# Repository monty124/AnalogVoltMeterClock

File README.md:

# AnalogVoltMeterClock
An AnalogVoltMeterClock 🤷‍♂️

# What is this?
Just a fun project to show the time in another way

Inspiration from:

- https://hackaday.io/project/163977-esp8266-wifi-ntp-voltmeter-clock
- https://michaelteeuw.nl/post/what-time-is-it-fathers-day
- https://github.com/MichMich/AnalogVoltMeterClock

# I want one

Sure, youll need:

### BOM

- An Enclosure, it needs to be big enough to fit the analog dials as well as the PCB (100x60) <br>
  There is a printable one that MAY work here https://www.thingiverse.com/thing:3437800 BUT i am unsure if my PCB will fit this enclosure. Zip Files are committed in this git repo if you want to try it; OR build without the PCB and hard wire to the ESP module and use this one.
- Optional 3D printed back or solid back, (make room for your power connection!)
- 3x Analog Voltmeter SO-45 style gauges (voltage unimportant) <br>
  https://www.aliexpress.com/item/1005003489268646.html <br>
  
- 3x 3.9K Resistors OR any value between 2 - 5 K however you will need to work out your own calibration matrix
- PCB (gerber files are included [here](/AnalogVoltMeterClock/Gerber))

- "SW-420" Vibration Sensor <br>
  https://www.aliexpress.com/item/1005006205428052.html <br>
  
- "6 Pin" USB C Power socket OR panel mount DC socket and 5V power supply (use PWR header and omit USB) <br>
   <br>
  https://www.aliexpress.com/item/32976798070.html
- 3.5mm Pitch 2P and 3P Screw Terminals <br>
   https://www.aliexpress.com/item/4000874208361.html <br>
    
- 1x FreeNove ESP32 WROOM 32E (not S3 variants) <br>
  https://store.freenove.com/products/fnk0090 or on Aliexpress<br>
  Note, Pinout of PCB is not compatible with other ESP modules like DevKit, etc <br>
 
- SN74AHCT125N IC <br>
 https://www.digikey.com.au/en/products/detail/texas-instruments/SN74AHCT125N/375798
- suitable 14Pin DIP Socket (optional) e.g. <br>
 https://www.digikey.com.au/en/products/detail/cnc-tech/245-14-1-03/3441580 <br>
- 2.54 Headers and Sockets (optional) <br>
  Socket 2x 20 pin for ESP module <br>
  Header for Power (if desired) <br>
- SK6812 LED's (ON PCB!) (if other variants are used like WS2812B you will need to debug the light: code block slightly) <br>
  https://esphome.io/components/light/index.html <br>
  n.b the White Channel is not important, can be WW, CW or NW <br>
  https://www.aliexpress.com/item/32961777888.html <br>
  https://www.aliexpress.com/item/1005002509850925.html <br>
   <br>
  <br>
- Silicone Hookup Wire and Crimps
- ESPHome Dev environment to build and deploy the Image <br>
  https://esphome.io/guides/getting_started_command_line <br>
  https://esphome.io/guides/getting_started_hassio <br>
- Cut and Printed [stickers](/Gauges)) to replace voltmeter gauge; use the PDF or the svg can be edited and printed with Inkscape https://inkscape.org/ <br>

# How To!

- Obtain your BOM items
- Build your enclosure!
- Dissasemble your gauges, replace the existing resistors with the 3.9K resistors, wire and mount your LED's <br>
   <br>
- Stick your gauge sticker over the original faceplace
- REASSEMBLE! <br>
   <br>
- Assemble your PCB
- Write the Base esphome image to your module https://web.esphome.io/ and connect to WIFI remember to also to include the `.h` files
- Edit the ESPHome Yaml file where required 
  - set MIN and MAX PWM
  - (optional) RGBW and Bright values
  - TimeZone (if not AEST) and or change to sntp see below
  - Disable Home Assistant api (remove encryption and key) if you dont use HA (also change time to sntp) <br>
    i.e:
    ```
    - platform: sntp
    #- platform: homeassistant
    timezone: Australia/Brisbane
    ```

- Build and Write the config to the module
- All should be working! 
- Connect to the Module Web Page and set LED colour
- Import into Home Assistant (optional)

# Calibration

[Excel sheets](/SpreadSheets) added to help calibrate! 

## PWM

- Use the Module web page to test values:
- Set Calibrate to ON <br>
  <br>
- Find your MIN and MAX needle values for Hour, Minute and Second using the HOUR CALIBRATE, MIN CALIBRATE and SEC CALIBRATE Sliders, take note of the blue number <br>
 <br>
- Min the needle should be set to the desired minimum value (for example minimum values): <br>
 <br>
- Max is the same but the Maximum value (12 for Hour, and 60 for Min and Sec) <br>
- These numbers are recorded in the yaml file: <br>
   <br>
- This is the minimum amount of calibration required however you MUST set the "Average Gauge Needle" option to ON!

## Fine Tuned Calibration

- Continue to find each value and create a value MAP. <br>
- For example for Hour:
- find each PWM value for each number from 1 to 12
- Record the PWM values in `writeHandler.h` under `const int HOUR_NEEDLE[]` where each value represents the hour, the MAP works as such: <br>
  
  ```
  Midnight (12), 1 AM, 2, 3, 4, 5, 6, 7, 8, 9, 10, 11, 12, 1 PM, 2, 3, 4, 5, 6, 7, 8, 9, 10, 11
  ```

  DO NOT ALTER `const int HOUR_LOOKUP[]`

For Minute and Second there is a map for each second/minute, this can be performed by finding each PWM value per 5 interval (5 Seconds or 5 Minutes) THEN averaging the seconds and minutes in between. You are looking for as even as a spread between each minute/second represented as a whole integer 

  For example:

| Hour | PWM | Comment |
| :--: | :--: | :--: | 
| 0 | 14 | measured |
| 5 | 30 | measured |
| 10 | 48 | measured |

| Hour | PWM | Comment |
| :--: | :--: | :--: | 
| 0 | 14 | measured |
| 1 | 17 | averaged |
| 2 | 20 | averaged |
| 3 | 23 | averaged |
| 4 | 26 | averaged |
| 5 | 30 | measured |

Create a Map of all values and replace `const int SECOND_NEEDLE[]` and `const int MINUTE_NEEDLE[]`

You are able to fine tune the needle using the screw on the front of the dial

## LED

- enable LED: Calibrate
- To find your desired colour use 
  - LED: Blue Level
  - LED: Colour Brightness
  - LED: Green Level
  - LED: Red Level
  - LED: White Level

This value will save into eeprom but will not be retained if the module is reflashed, you can code these into the globals but!

## U2 Jumpers

The SN74AHCT125N can be a little .... sensitive and as we are only using one input and output a circuit has been built in where by if you accidently blow input/output 1A/1Y you can reconfgure the jumpers to use the other inputs and outputs! This avoids you throwing away an IC because one IO has failed. Hopefully.

 <br>

This table should help explain what jumpers you need to bridge. Note you will need to CUT the DEFAULT jumpers on JP3 and JP4 if you wish to use IO's 3 or 4, and cut the DEFAULT jumper on JP1 and JP5 to use IO 2

 <br>

More info can be found in the datasheet in the [repo](/sn74ahct125.pdf)

## To Do!

- Integrate a PCF8563 RTC module option for time keeping offline https://www.aliexpress.com/item/1005006438572175.html
- Code Improvements and tidy up
- ~~Excel sheet for calibration~~
- ~~Document matrix for IC~~
- 3D rear cover (STARTED!)
- Actual Assembly (still waiting on parts!)
- gif of movement

## I Wanna Contribute!

Sure, fork the repo and do ya thing then request a PR to merge!

## I found a bug or an Improvement!

As above OR open an Issue and lets see if we can fix

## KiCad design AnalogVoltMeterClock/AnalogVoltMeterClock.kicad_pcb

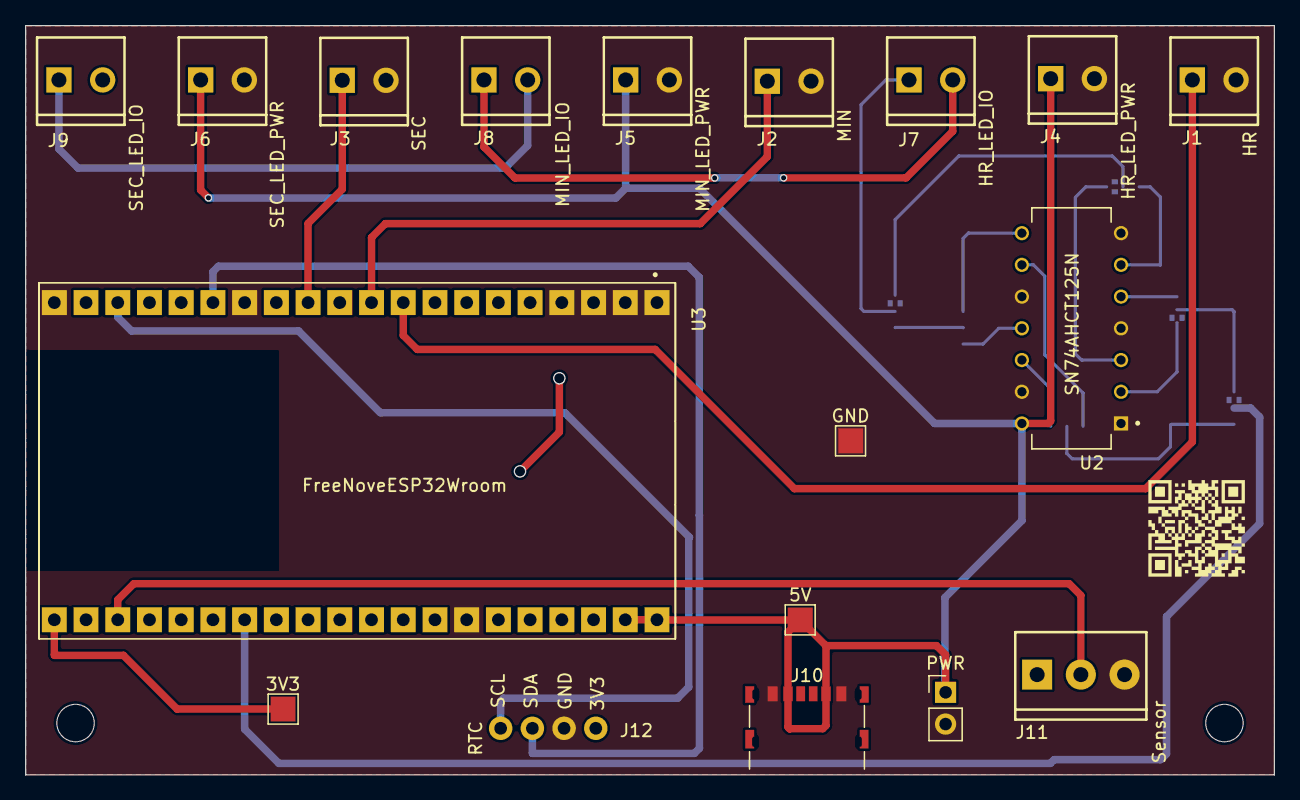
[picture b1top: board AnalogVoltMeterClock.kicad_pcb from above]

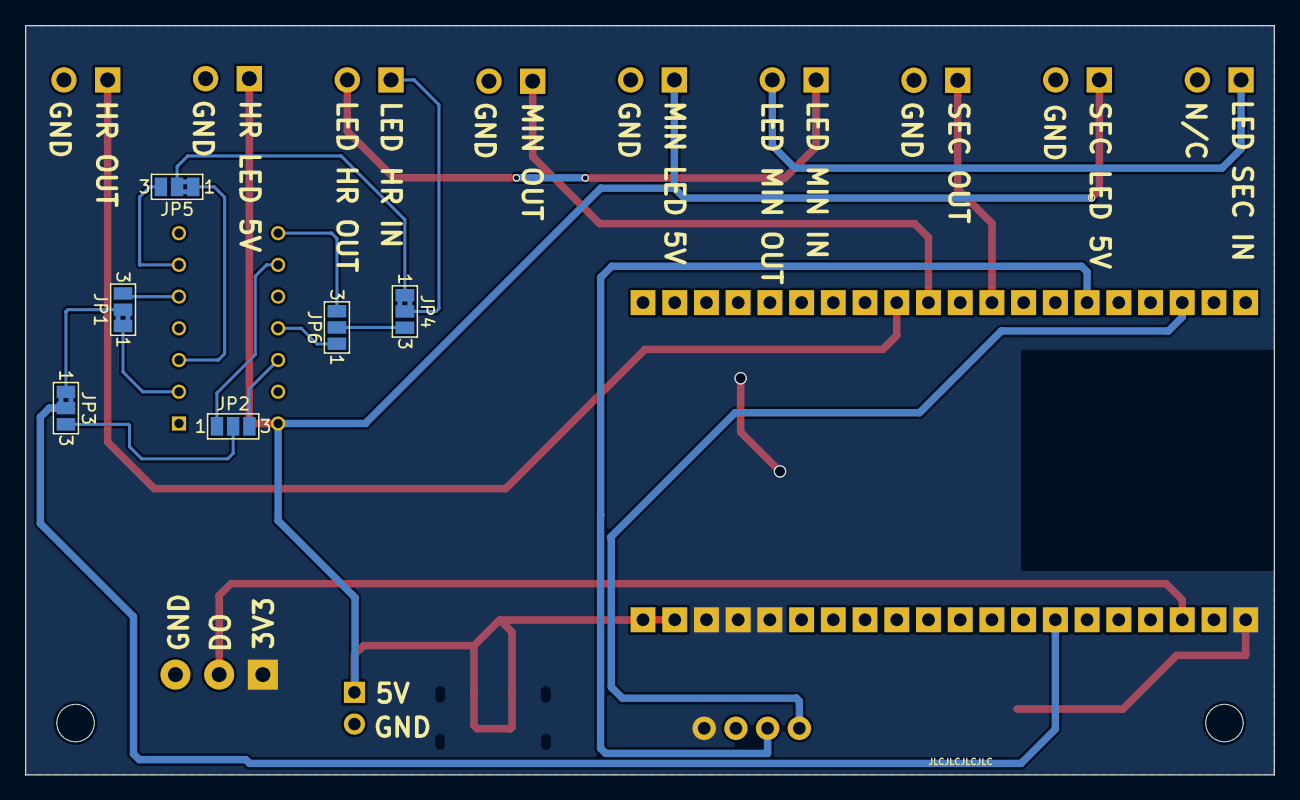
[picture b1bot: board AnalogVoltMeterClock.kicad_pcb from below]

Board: 2 copper layers, 100.0 x 60.0 mm, 26 parts (6 on the bottom side), 25 nets.

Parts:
3V3, 5V: TestPoint_Pad_2.0x2.0mm
GND: TestPoint_Pad_2.0x2.0mm
H1, H2: MountingHole; MountingHole_3mm
J1: HR; SCREWTERMINAL-3.5MM-2
J2: MIN; SCREWTERMINAL-3.5MM-2
J3: SEC; SCREWTERMINAL-3.5MM-2
J4: HR_LED_PWR; SCREWTERMINAL-3.5MM-2
J5: MIN_LED_PWR; SCREWTERMINAL-3.5MM-2
J6: SEC_LED_PWR; SCREWTERMINAL-3.5MM-2
J7: HR_LED_IO; SCREWTERMINAL-3.5MM-2
J8: MIN_LED_IO; SCREWTERMINAL-3.5MM-2
J9: SEC_LED_IO; SCREWTERMINAL-3.5MM-2
J10: PowerIn; USB_C_Receptacle_GCT_USB4135-GF-A_6P_TopMnt_Thru
J11: Sensor; SCREWTERMINAL-3.5MM-3
J12: RTC; 1X04
JP1: IO1_2-In; SolderJumper-3_P1.3mm_Bridged2Bar12_Pad1.0x1.5mm_NumberLabe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
JP2: IO3_4-In; SolderJumper-3_P1.3mm_Open_Pad1.0x1.5mm_NumberLabels
JP3, JP4: IO_12_34; SolderJumper-3_P1.3mm_Bridged2Bar12_Pad1.0x1.5mm_NumberLabe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
JP5: IO1_2-Out; SolderJumper-3_P1.3mm_Bridged2Bar12_Pad1.0x1.5mm_NumberLabe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
JP6: IO3_4-Out; SolderJumper-3_P1.3mm_Open_Pad1.0x1.5mm_NumberLabels
PWR: PinHeader_1x02_P2.54mm_Vertical
U2: SN74AHCT125N; DIP794W45P254L1930H508Q14
U3: FreeNoveESP32Wroom

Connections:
1A: JP1.1 (A), U2.2 (1A)
1Y: JP5.1 (A), U2.3 (1Y)
2A: JP1.3 (B), U2.5 (2A)
2Y: JP5.3 (B), U2.6 (2Y)
3A: JP2.1 (A), U2.9 (3A)
3V3: 3V3.1, J11.1, J12.1, U3.21 (3V3), U3.36 (3V3), U3.37 (3V3), U3.38 (3V3)
3Y: JP6.3 (B), U2.8 (3Y)
4A: JP2.3 (B), U2.12 (4A)
4Y: JP6.1 (A), U2.11 (4Y)
+5V: 5V.1, J4.1, J5.1, J6.1, J10.A9 (VBUS), J10.B9 (VBUS), PWR.1, U2.14 (VCC), U3.39 (VIN), U3.40 (VIN)
GND: GND.1, J1.2, J2.2, J3.2, J4.2, J5.2, J6.2, J10.A12 (GND), J10.B12 (GND), J11.3, J12.2, PWR.2, U2.1 (1~OE), U2.4 (2~OE), U2.7 (GND), U2.10 (3~OE), U2.13 (4~OE), U3.1 (GND), U3.2 (GND), U3.3 (GND), U3.4 (GND), U3.14 (GND), U3.20 (GND), U3.34 (GND)
HR: J1.1, U3.9 (D16)
JP1_O: JP1.2 (C), JP3.1 (A)
JP2_O: JP2.2 (C), JP3.3 (B)
JP5_O: JP4.1 (A), JP5.2 (C)
JP6_O: JP4.3 (B), JP6.2 (C)
LED: J7.1, JP4.2 (C)
LED_O: JP3.2 (C), U3.27 (D32)
MIN: J2.1, U3.10 (D17)
MIN_IN: J7.2, J8.1
MIN_OUT: J8.2, J9.1
SCL: J12.4, U3.18 (D22)
SDA: J12.3, U3.15 (D21)
SEC: J3.1, U3.12 (D18)
SEN: J11.2, U3.23 (D36)

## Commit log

2024-06-15 initial
2024-06-15 Create Schematic.pdf
    Added Schematic
2024-06-16 Spreadsheets added!
2024-06-16 additional changes
